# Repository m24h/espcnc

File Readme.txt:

A 3D printer or CNC controller using ESP32 module
Using DMA/FIFO buffered I2S port to output step pulses

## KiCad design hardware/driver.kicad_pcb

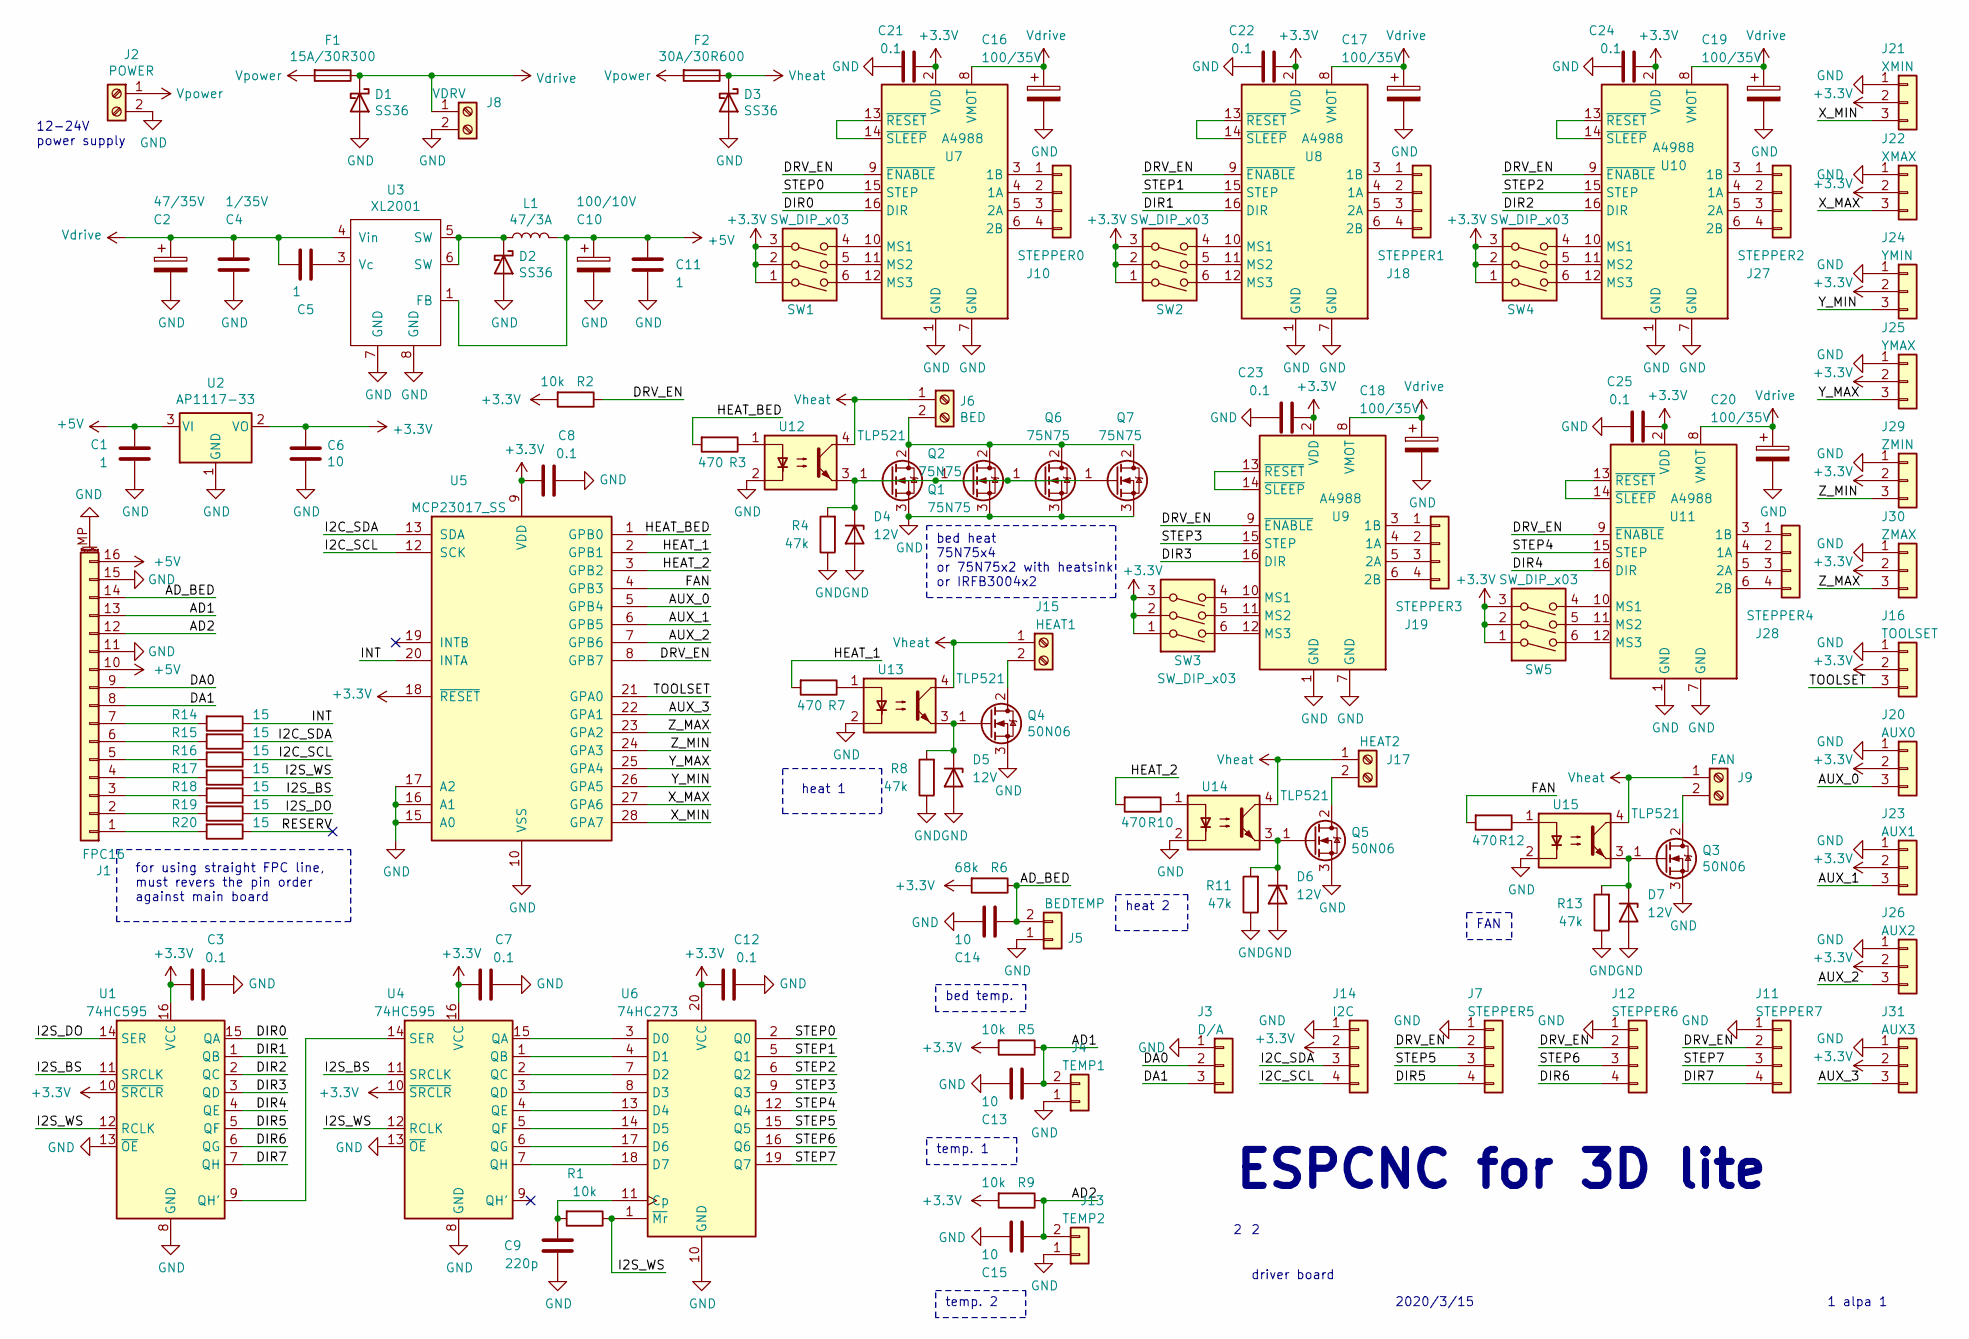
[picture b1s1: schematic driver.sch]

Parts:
C1, C5, C11: 1; C_0805_2012Metric_Pad1.15x1.40mm_HandSolder
C2: 47/35V; CP_Radial_D6.3mm_P2.50mm
C3, C7, C8, C12, C21, C22, C23, C24, C25: 0.1; C_0603_1608Metric_Pad1.05x0.95mm_HandSolder
C4: 1/35V; C_0805_2012Metric_Pad1.15x1.40mm_HandSolder
C6, C13, C14, C15: 10; C_1206_3216Metric_Pad1.42x1.75mm_HandSolder
C9: 220p; C_0603_1608Metric_Pad1.05x0.95mm_HandSolder
C10: 100/10V; CP_Radial_D6.3mm_P2.50mm
C16, C17, C18, C19, C20: 100/35V; CP_Radial_D6.3mm_P2.50mm
D1, D2, D3: SS36; D_SMA_Handsoldering
D4, D5, D6, D7: 12V; D_DO-41_SOD81_P2.54mm_Vertical_KathodeUp
F1: 15A/30R300; Fuse_Bourns_MF-RG300
F2: 30A/30R600; Fuse_Bourns_MF-RG500
J1: FPC16; Molex_200528-0160_1x16-1MP_P1.00mm_Horizontal
J2: POWER; TerminalBlock_bornier-2_P5.08mm
J3: D/A; PinHeader_1x03_P2.54mm_Vertical
J4: TEMP1; PinHeader_1x02_P2.54mm_Vertical
J5: BEDTEMP; PinHeader_1x02_P2.54mm_Vertical
J6: BED; TerminalBlock_bornier-2_P5.08mm
J7: STEPPER5; PinHeader_1x04_P2.54mm_Vertical
J8: VDRV; TerminalBlock_bornier-2_P5.08mm
J9: FAN; TerminalBlock_bornier-2_P5.08mm
J10: STEPPER0; PinHeader_1x04_P2.54mm_Vertical
J11: STEPPER7; PinHeader_1x04_P2.54mm_Vertical
J12: STEPPER6; PinHeader_1x04_P2.54mm_Vertical
J13: TEMP2; PinHeader_1x02_P2.54mm_Vertical
J14: I2C; PinHeader_1x04_P2.54mm_Vertical
J15: HEAT1; TerminalBlock_bornier-2_P5.08mm
J16: TOOLSET; PinHeader_1x03_P2.54mm_Vertical
J17: HEAT2; TerminalBlock_bornier-2_P5.08mm
J18: STEPPER1; PinHeader_1x04_P2.54mm_Vertical
J19: STEPPER3; PinHeader_1x04_P2.54mm_Vertical
J20: AUX0; PinHeader_1x03_P2.54mm_Vertical
J21: XMIN; PinHeader_1x03_P2.54mm_Vertical
J22: XMAX; PinHeader_1x03_P2.54mm_Vertical
J23: AUX1; PinHeader_1x03_P2.54mm_Vertical
J24: YMIN; PinHeader_1x03_P2.54mm_Vertical
J25: YMAX; PinHeader_1x03_P2.54mm_Vertical
J26: AUX2; PinHeader_1x03_P2.54mm_Vertical
J27: STEPPER2; PinHeader_1x04_P2.54mm_Vertical
J28: STEPPER4; PinHeader_1x04_P2.54mm_Vertical
J29: ZMIN; PinHeader_1x03_P2.54mm_Vertical
J30: ZMAX; PinHeader_1x03_P2.54mm_Vertical
J31: AUX3; PinHeader_1x03_P2.54mm_Vertical
L1: 47/3A; L_Toroid_Horizontal_D7.8mm_P13.00mm_Diameter9-5mm_Amidon-T30
Q1, Q2, Q6, Q7: 75N75; TO-220-3_Vertical
Q3, Q4, Q5: 50N06; TO-220-3_Vertical
R1, R2, R5, R9: 10k; R_0603_1608Metric_Pad1.05x0.95mm_HandSolder
R3, R7, R10, R12: 470; R_0603_1608Metric_Pad1.05x0.95mm_HandSolder
R4, R8, R11, R13: 47k; R_0603_1608Metric_Pad1.05x0.95mm_HandSolder
R6: 68k; R_0603_1608Metric_Pad1.05x0.95mm_HandSolder
R14, R15, R16, R17, R18, R19, R20: 15; R_0603_1608Metric_Pad1.05x0.95mm_HandSolder
SW1, SW2, SW3, SW4, SW5: SW_DIP_x03; DIP-6_W7.62mm
U1, U4: 74HC595; SOP-16_4.55x10.3mm_P1.27mm
U2: AP1117-33; SOT-223-3_TabPin2
U3: XL2001; SOP-8_5.28x5.23mm_P1.27mm
U5: MCP23017_SS; SSOP-28_5.3x10.2mm_P0.65mm
U6: 74HC273; SOIC-20W_7.5x12.8mm_P1.27mm
U7, U8, U9, U10, U11: A4988; Pololu_Breakout-16_15.2x20.3mm
U12, U13, U14, U15: TLP521; DIP-4_W7.62mm

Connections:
+3V3: C3.2, C6.1, C7.2, C8.2, C12.2, C21.1, C22.1, C23.1, C24.1, C25.1, J14.2, J16.2, J20.2, J21.2, J22.2, J23.2, J24.2, J25.2, J26.2, J29.2, J30.2, J31.2, R2.2, R5.2, R6.2, R9.2, SW1.1, SW1.2, SW1.3, SW2.1, SW2.2, SW2.3, SW3.1, SW3.2, SW3.3, SW4.1, SW4.2, SW4.3, SW5.1, SW5.2, SW5.3, U1.10 (~SRCLR), U1.16 (VCC), U2.2 (VO), U4.10 (~SRCLR), U4.16 (VCC), U5.9 (VDD), U5.18 (~RESET~), U6.20 (VCC), U7.2 (VDD), U8.2 (VDD), U9.2 (VDD), U10.2 (VDD), U11.2 (VDD)
+5V: C1.1, C10.1, C11.1, J1.10, J1.16, L1.2, U2.3 (VI), U3.1 (FB)
/AD1: C13.1, J1.13, J4.2, R5.1
/AD2: C15.1, J1.12, J13.2, R9.1
/AD_BED: C14.1, J1.14, J5.2, R6.1
/AUX_0: J20.3, U5.5 (GPB4)
/AUX_1: J23.3, U5.6 (GPB5)
/AUX_2: J26.3, U5.7 (GPB6)
/AUX_3: J31.3, U5.22 (GPA1)
/DA0: J1.9, J3.2
/DA1: J1.8, J3.3
/DIR0: U1.15 (QA), U7.16 (DIR)
/DIR1: U1.1 (QB), U8.16 (DIR)
/DIR2: U1.2 (QC), U10.16 (DIR)
/DIR3: U1.3 (QD), U9.16 (DIR)
/DIR4: U1.4 (QE), U11.16 (DIR)
/DIR5: J7.4, U1.5 (QF)
/DIR6: J12.4, U1.6 (QG)
/DIR7: J11.4, U1.7 (QH)
/DRV_EN: J7.2, J11.2, J12.2, R2.1, U5.8 (GPB7), U7.9 (~ENABLE), U8.9 (~ENABLE), U9.9 (~ENABLE), U10.9 (~ENABLE), U11.9 (~ENABLE)
/FAN: R12.2, U5.4 (GPB3)
/HEAT_1: R7.2, U5.2 (GPB1)
/HEAT_2: R10.2, U5.3 (GPB2)
/HEAT_BED: R3.2, U5.1 (GPB0)
/I2C_SCL: J14.4, R16.1, U5.12 (SCK)
/I2C_SDA: J14.3, R15.1, U5.13 (SDA)
/I2S_BS: R18.1, U1.11 (SRCLK), U4.11 (SRCLK)
/I2S_DO: R19.1, U1.14 (SER)
/I2S_WS: R1.1, R17.1, U1.12 (RCLK), U4.12 (RCLK), U6.1 (~Mr)
/INT: R14.1, U5.20 (INTA)
/RESERV: R20.1
/STEP0: U6.2 (Q0), U7.15 (STEP)
/STEP1: U6.5 (Q1), U8.15 (STEP)
/STEP2: U6.6 (Q2), U10.15 (STEP)
/STEP3: U6.9 (Q3), U9.15 (STEP)
/STEP4: U6.12 (Q4), U11.15 (STEP)
/STEP5: J7.3, U6.15 (Q5)
/STEP6: J12.3, U6.16 (Q6)
/STEP7: J11.3, U6.19 (Q7)
/TOOLSET: J16.3, U5.21 (GPA0)
/X_MAX: J22.3, U5.27 (GPA6)
/X_MIN: J21.3, U5.28 (GPA7)
/Y_MAX: J25.3, U5.25 (GPA4)
/Y_MIN: J24.3, U5.26 (GPA5)
/Z_MAX: J30.3, U5.23 (GPA2)
/Z_MIN: J29.3, U5.24 (GPA3)
GND: C1.2, C2.2, C3.1, C4.2, C6.2, C7.1, C8.1, C9.1, C10.2, C11.2, C12.1, C13.2, C14.2, C15.2, C16.2, C17.2, C18.2, C19.2, C20.2, C21.2, C22.2, C23.2, C24.2, C25.2, D1.2 (A), D2.2 (A), D3.2 (A), D4.2 (A), D5.2 (A), D6.2 (A), D7.2 (A), J1.11, J1.15, J1.MP (MountPin), J2.2, J3.1, J4.1, J5.1, J7.1, J8.2, J11.1, J12.1, J13.1, J14.1, J16.1, J20.1, J21.1, J22.1, J23.1, J24.1, J25.1, J26.1, J29.1, J30.1, J31.1, Q1.3 (S), Q2.3 (S), Q3.3 (S), Q4.3 (S), Q5.3 (S), Q6.3 (S), Q7.3 (S), R4.1, R8.1, R11.1, R13.1, U1.8 (GND), U1.13 (~OE), U2.1 (GND), U3.7 (GND), U3.8 (GND), U4.8 (GND), U4.13 (~OE), U5.10 (VSS), U5.15 (A0), U5.16 (A1), U5.17 (A2), U6.10 (GND), U7.1 (GND), U7.7 (GND), U8.1 (GND), U8.7 (GND), U9.1 (GND), U9.7 (GND), U10.1 (GND), U10.7 (GND), U11.1 (GND), U11.7 (GND), U12.2, U13.2, U14.2, U15.2
unnamed: C5.1, U3.3 (Vc)
unnamed: C9.2, R1.2, U6.11 (Cp)
unnamed: D2.1 (K), L1.1, U3.5 (SW), U3.6 (SW)
unnamed: D4.1 (K), Q1.1 (G), Q2.1 (G), Q6.1 (G), Q7.1 (G), R4.2, U12.3
unnamed: D5.1 (K), Q4.1 (G), R8.2, U13.3
unnamed: D6.1 (K), Q5.1 (G), R11.2, U14.3
unnamed: D7.1 (K), Q3.1 (G), R13.2, U15.3
unnamed: J1.1, R20.2
unnamed: J1.2, R19.2
unnamed: J1.3, R18.2
unnamed: J1.4, R17.2
unnamed: J1.5, R16.2
unnamed: J1.6, R15.2
unnamed: J1.7, R14.2
unnamed: J6.2, Q1.2 (D), Q2.2 (D), Q6.2 (D), Q7.2 (D)
unnamed: J9.2, Q3.2 (D)
unnamed: J10.1, U7.3 (1B)
unnamed: J10.2, U7.4 (1A)
unnamed: J10.3, U7.5 (2A)
unnamed: J10.4, U7.6 (2B)
unnamed: J15.2, Q4.2 (D)
unnamed: J17.2, Q5.2 (D)
unnamed: J18.1, U8.3 (1B)
unnamed: J18.2, U8.4 (1A)
unnamed: J18.3, U8.5 (2A)
unnamed: J18.4, U8.6 (2B)
unnamed: J19.1, U9.3 (1B)
unnamed: J19.2, U9.4 (1A)
unnamed: J19.3, U9.5 (2A)
unnamed: J19.4, U9.6 (2B)
unnamed: J27.1, U10.3 (1B)
unnamed: J27.2, U10.4 (1A)
unnamed: J27.3, U10.5 (2A)
unnamed: J27.4, U10.6 (2B)
unnamed: J28.1, U11.3 (1B)
unnamed: J28.2, U11.4 (1A)
unnamed: J28.3, U11.5 (2A)
unnamed: J28.4, U11.6 (2B)
unnamed: R3.1, U12.1
unnamed: R7.1, U13.1
unnamed: R10.1, U14.1
unnamed: R12.1, U15.1
unnamed: SW1.4, U7.10 (MS1)
unnamed: SW1.5, U7.11 (MS2)
unnamed: SW1.6, U7.12 (MS3)
unnamed: SW2.4, U8.10 (MS1)
unnamed: SW2.5, U8.11 (MS2)
unnamed: SW2.6, U8.12 (MS3)
unnamed: SW3.4, U9.10 (MS1)
unnamed: SW3.5, U9.11 (MS2)
unnamed: SW3.6, U9.12 (MS3)
unnamed: SW4.4, U10.10 (MS1)
unnamed: SW4.5, U10.11 (MS2)
unnamed: SW4.6, U10.12 (MS3)
unnamed: SW5.4, U11.10 (MS1)
unnamed: SW5.5, U11.11 (MS2)
unnamed: SW5.6, U11.12 (MS3)
unnamed: U1.9 (QH'), U4.14 (SER)
unnamed: U4.1 (QB), U6.4 (D1)
unnamed: U4.2 (QC), U6.7 (D2)
unnamed: U4.3 (QD), U6.8 (D3)
unnamed: U4.4 (QE), U6.13 (D4)
unnamed: U4.5 (QF), U6.14 (D5)
unnamed: U4.6 (QG), U6.17 (D6)
unnamed: U4.7 (QH), U6.18 (D7)
unnamed: U4.15 (QA), U6.3 (D0)
unnamed: U7.13 (~RESET), U7.14 (~SLEEP)
unnamed: U8.13 (~RESET), U8.14 (~SLEEP)
unnamed: U9.13 (~RESET), U9.14 (~SLEEP)
unnamed: U10.13 (~RESET), U10.14 (~SLEEP)
unnamed: U11.13 (~RESET), U11.14 (~SLEEP)
Vdrive: C2.1, C4.1, C5.2, C16.1, C17.1, C18.1, C19.1, C20.1, D1.1 (K), F1.1, J8.1, U3.4 (Vin), U7.8 (VMOT), U8.8 (VMOT), U9.8 (VMOT), U10.8 (VMOT), U11.8 (VMOT)
Vheat: D3.1 (K), F2.1, J6.1, J9.1, J15.1, J17.1, U12.4, U13.4, U14.4, U15.4
Vpower: F1.2, F2.2, J2.1

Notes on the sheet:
ESPCNC for 3D lite
2020/3/15
driver board
1 alpa 1
bed temp.
12-24V power supply
bed heat 75N75x4 or 75N75x2 with heatsink or IRFB3004x2
heat 2
heat 1
temp. 1
temp. 2
FAN
for using straight FPC line, must revers the pin order against main board

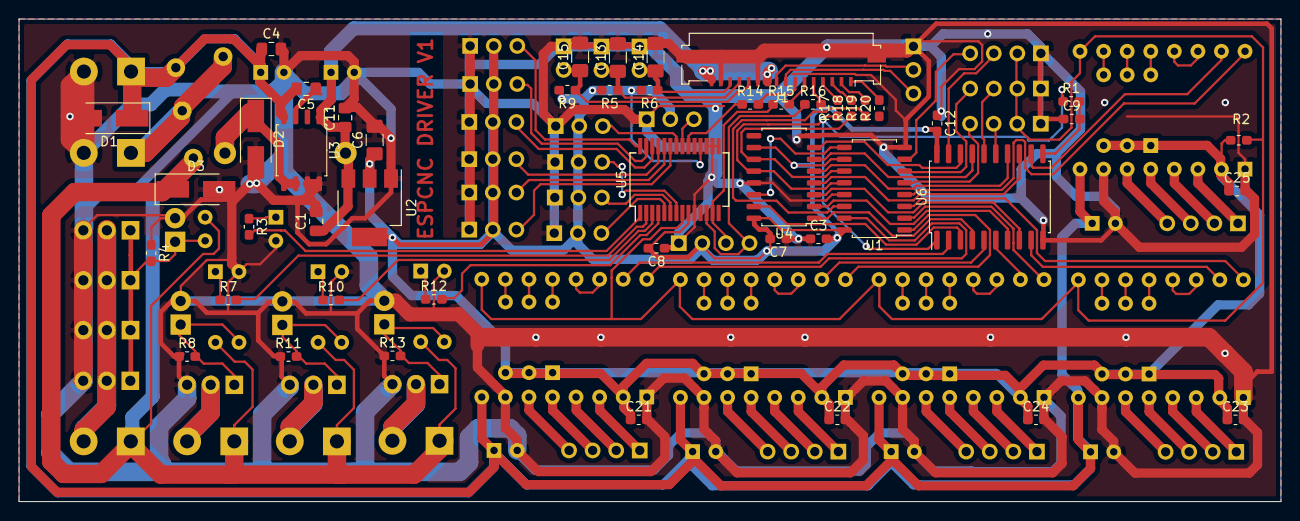
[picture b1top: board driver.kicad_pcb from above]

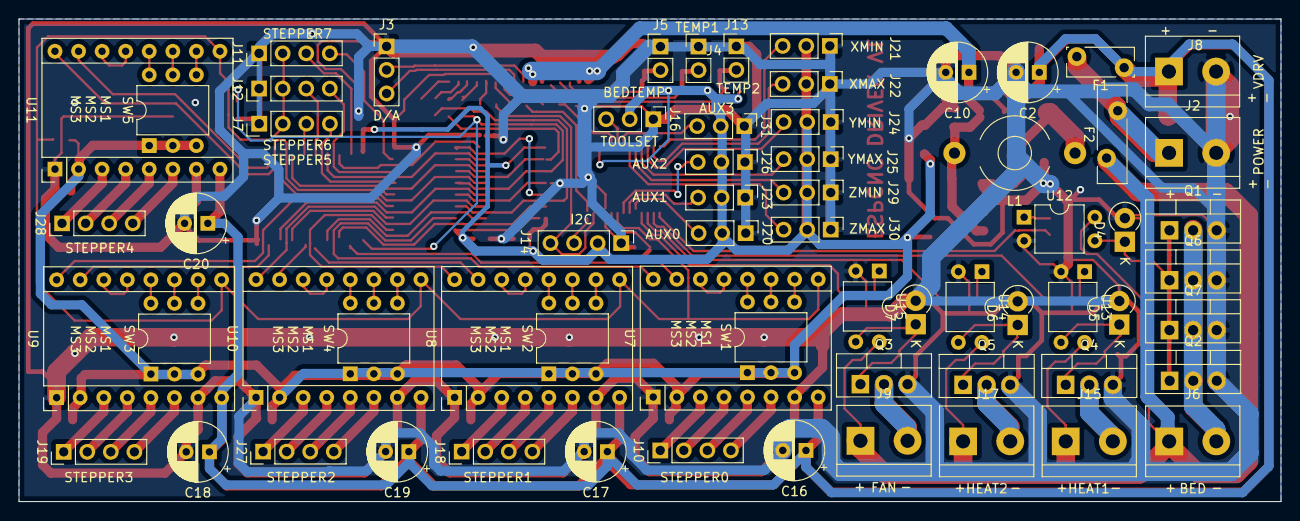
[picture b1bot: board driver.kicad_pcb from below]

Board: 2 copper layers, 136.0 x 52.0 mm, 113 parts (65 on the bottom side), 120 nets.

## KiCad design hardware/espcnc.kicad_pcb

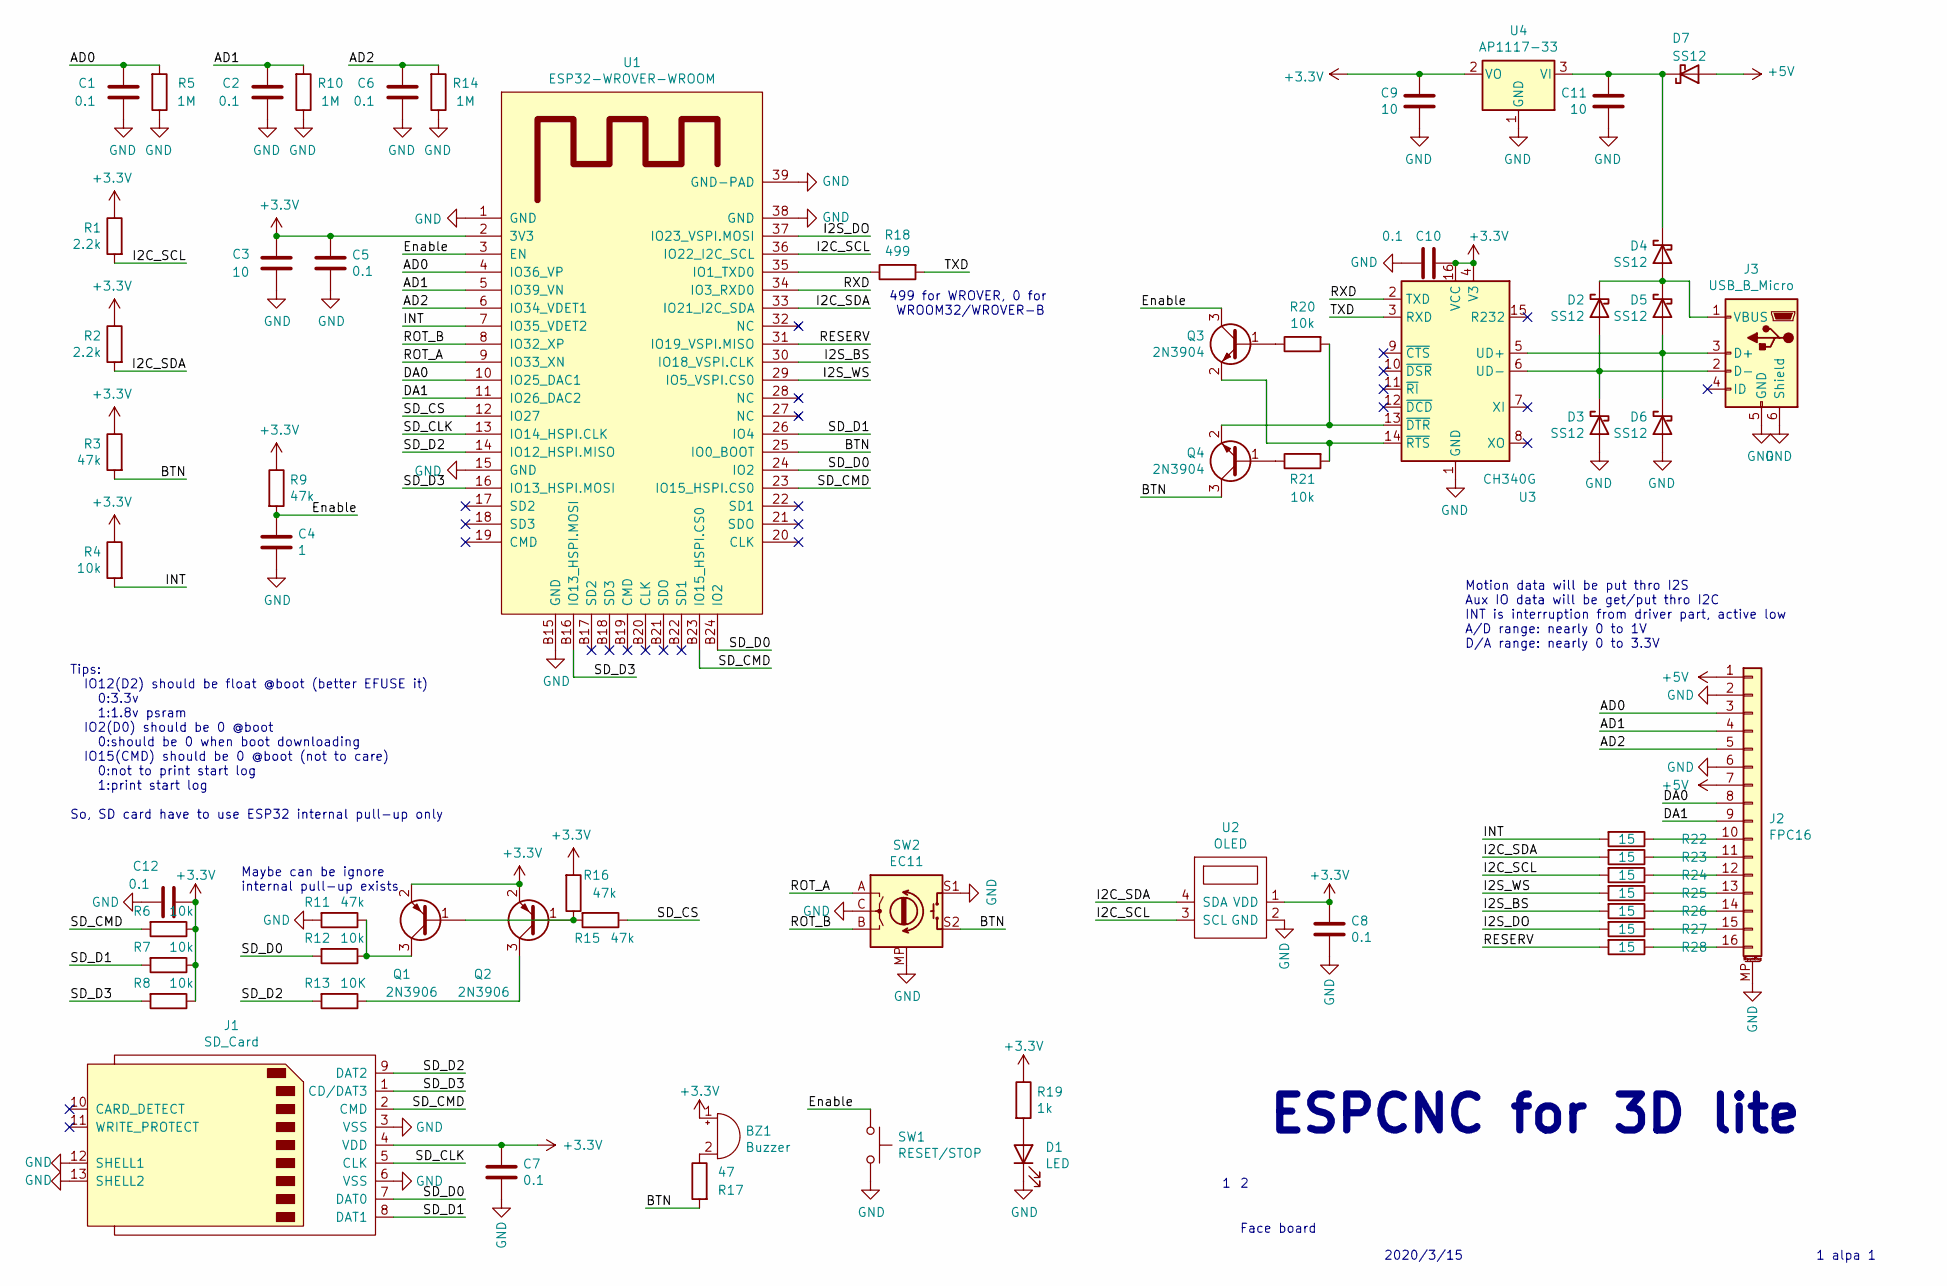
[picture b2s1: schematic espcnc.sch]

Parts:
BZ1: Buzzer; Buzzer_12x9.5RM7.6
C1, C2, C5, C6, C7, C8, C10, C12: 0.1; C_0603_1608Metric_Pad1.05x0.95mm_HandSolder
C3, C9, C11: 10; C_1206_3216Metric_Pad1.42x1.75mm_HandSolder
C4: 1; C_0805_2012Metric_Pad1.15x1.40mm_HandSolder
D1: LED; LED_D1.8mm_W3.3mm_H2.4mm
D2, D3, D4, D5, D6, D7: SS12; D_SMA_Handsoldering
J1: SD_Card; SD_CARD
J2: FPC16; Molex_200528-0160_1x16-1MP_P1.00mm_Horizontal
J3: USB_B_Micro; USB_Micro-B_Molex-105017-0001
Q1, Q2: 2N3906; SOT-23
Q3, Q4: 2N3904; SOT-23
R1, R2: 2.2k; R_0603_1608Metric_Pad1.05x0.95mm_HandSolder
R3, R9, R11, R15, R16: 47k; R_0603_1608Metric_Pad1.05x0.95mm_HandSolder
R4, R6, R7, R8, R12, R20, R21: 10k; R_0603_1608Metric_Pad1.05x0.95mm_HandSolder
R5, R10, R14: 1M; R_0603_1608Metric_Pad1.05x0.95mm_HandSolder
R13: 10K; R_0603_1608Metric_Pad1.05x0.95mm_HandSolder
R17: 47; R_0603_1608Metric_Pad1.05x0.95mm_HandSolder
R18: 499; R_0603_1608Metric_Pad1.05x0.95mm_HandSolder
R19: 1k; R_0603_1608Metric_Pad1.05x0.95mm_HandSolder
R22, R23, R24, R25, R26, R27, R28: 15; R_0603_1608Metric_Pad1.05x0.95mm_HandSolder
SW1: RESET/STOP; SW_PUSH-12mm
SW2: EC11; RotaryEncoder_Alps_EC11E-Switch_Vertical_H20mm_CircularMoun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
U1: ESP32-WROVER-WROOM
U2: OLED; 1.3_inch_i2c_oled_128x64_jinyichen
U3: CH340G; SOP-16_4.4x10.4mm_P1.27mm
U4: AP1117-33; SOT-223-3_TabPin2

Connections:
+3V3: BZ1.1 (-), C3.1, C5.1, C7.1, C8.1, C9.1, C10.2, C12.2, J1.4 (VDD), Q1.2 (E), Q2.2 (E), R1.1, R2.1, R3.1, R4.1, R6.1, R7.1, R8.1, R9.1, R16.2, R19.1, U1.2 (3V3), U2.1 (VDD), U3.4 (V3), U3.16 (VCC), U4.2 (VO)
+5V: D7.2 (A), J2.1, J2.7
/AD0: C1.1, J2.3, R5.2, U1.4 (IO36_VP)
/AD1: C2.1, J2.4, R10.2, U1.5 (IO39_VN)
/AD2: C6.1, J2.5, R14.2, U1.6 (IO34_VDET1)
/BTN: Q4.3 (C), R3.2, R17.2, SW2.S2, U1.25 (IO0_BOOT)
/DA0: J2.8, U1.10 (IO25_DAC1)
/DA1: J2.9, U1.11 (IO26_DAC2)
/Enable: C4.1, Q3.3 (C), R9.2, SW1.1, U1.3 (EN)
/I2C_SCL: R1.2, R24.2, U1.36 (IO22_I2C_SCL), U2.3 (SCL)
/I2C_SDA: R2.2, R23.2, U1.33 (IO21_I2C_SDA), U2.4 (SDA)
/I2S_BS: R26.2, U1.30 (IO18_VSPI.CLK)
/I2S_DO: R27.2, U1.37 (IO23_VSPI.MOSI)
/I2S_WS: R25.2, U1.29 (IO5_VSPI.CS0)
/INT: R4.2, R22.2, U1.7 (IO35_VDET2)
/RESERV: R28.2, U1.31 (IO19_VSPI.MISO)
/ROT_A: SW2.A, U1.9 (IO33_XN)
/ROT_B: SW2.B, U1.8 (IO32_XP)
/RXD: U1.34 (IO3_RXD0), U3.2 (TXD)
/SD_CLK: J1.5 (CLK), U1.13 (IO14_HSPI.CLK)
/SD_CMD: J1.2 (CMD), R6.2, U1.23 (IO15_HSPI.CS0), U1.B23 (IO15_HSPI.CS0)
/SD_CS: R15.1, U1.12 (IO27)
/SD_D0: J1.7 (DAT0), R12.2, U1.24 (IO2), U1.B24 (IO2)
/SD_D1: J1.8 (DAT1), R7.2, U1.26 (IO4)
/SD_D2: J1.9 (DAT2), R13.2, U1.14 (IO12_HSPI.MISO)
/SD_D3: J1.1 (CD/DAT3), R8.2, U1.16 (IO13_HSPI.MOSI), U1.B16 (IO13_HSPI.MOSI)
/TXD: R18.2, U3.3 (RXD)
GND: C1.2, C2.2, C3.2, C4.2, C5.2, C6.2, C7.2, C8.2, C9.2, C10.1, C11.2, C12.1, D1.1 (K), D3.2 (A), D6.2 (A), J1.3 (VSS), J1.6 (VSS), J1.12 (SHELL1), J1.13 (SHELL2), J2.2, J2.6, J2.MP (MountPin), J3.5 (GND), J3.6 (Shield), R5.1, R10.1, R11.2, R14.1, SW1.2, SW2.C, SW2.MP, SW2.S1, U1.1 (GND), U1.15 (GND), U1.38 (GND), U1.39 (GND-PAD), U1.B15 (GND), U2.2 (GND), U3.1 (GND), U4.1 (GND)
unnamed: BZ1.2 (+), R17.1
unnamed: C11.1, D4.1 (K), D7.1 (K), U4.3 (VI)
unnamed: D1.2 (A), R19.2
unnamed: D2.1 (K), D4.2 (A), D5.1 (K), J3.1 (VBUS)
unnamed: D2.2 (A), D3.1 (K), J3.2 (D-), U3.6 (UD-)
unnamed: D5.2 (A), D6.1 (K), J3.3 (D+), U3.5 (UD+)
unnamed: J2.10, R22.1
unnamed: J2.11, R23.1
unnamed: J2.12, R24.1
unnamed: J2.13, R25.1
unnamed: J2.14, R26.1
unnamed: J2.15, R27.1
unnamed: J2.16, R28.1
unnamed: Q1.1 (B), Q2.1 (B), R15.2, R16.1
unnamed: Q1.3 (C), R11.1, R12.1
unnamed: Q2.3 (C), R13.1
unnamed: Q3.1 (B), R20.1
unnamed: Q3.2 (E), R21.2, U3.14 (~RTS)
unnamed: Q4.1 (B), R21.1
unnamed: Q4.2 (E), R20.2, U3.13 (~DTR)
unnamed: R18.1, U1.35 (IO1_TXD0)

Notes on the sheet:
ESPCNC for 3D lite
2020/3/15
Face board
1 alpa 1
499 for WROVER, 0 for WROOM32/WROVER-B
Tips: IO12(D2) should be float @boot (better EFUSE it) 0:3.3v 1:1.8v psram IO2(D0) should be 0 @boot 0:should be 0 when boot downloading IO15(CMD) should be 0 @boot (not to care) 0:not to print start log 1:print start log So, SD card have to use ESP32 internal pull-up only
Maybe can be ignore internal pull-up exists
Motion data will be put thro I2S Aux IO data will be get/put thro I2C INT is interruption from driver part, active low A/D range: nearly 0 to 1V D/A range: nearly 0 to 3.3V

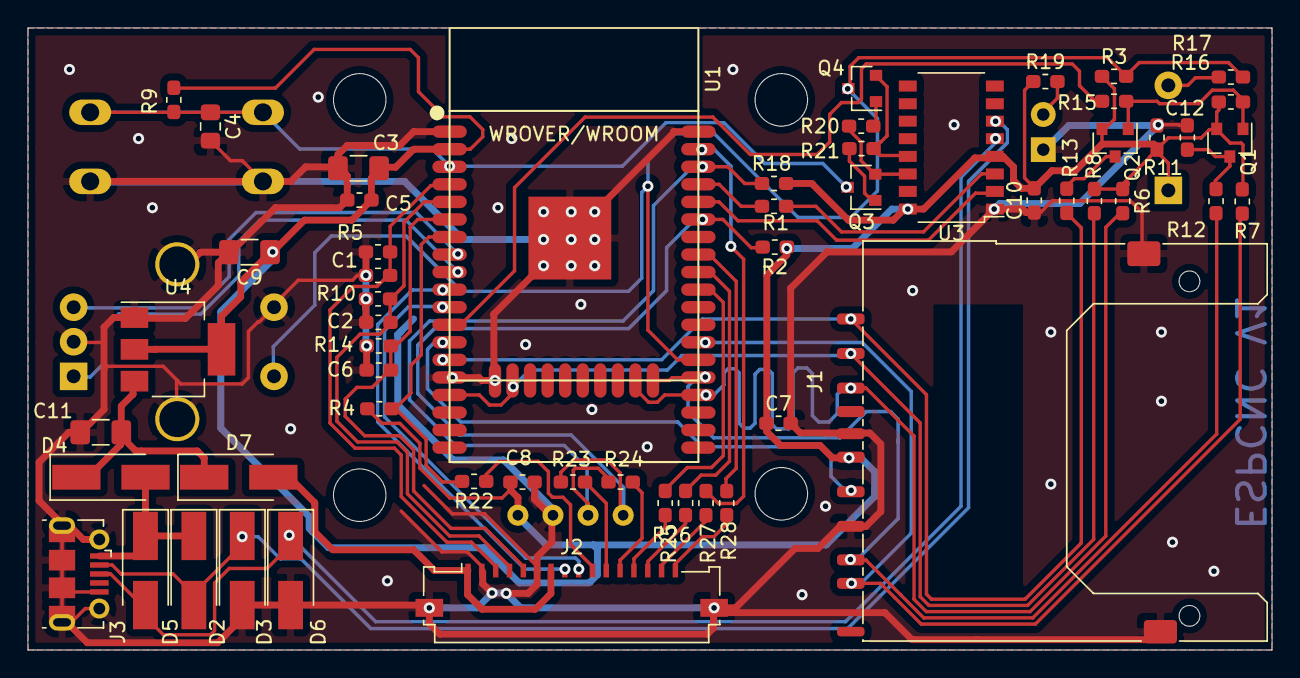
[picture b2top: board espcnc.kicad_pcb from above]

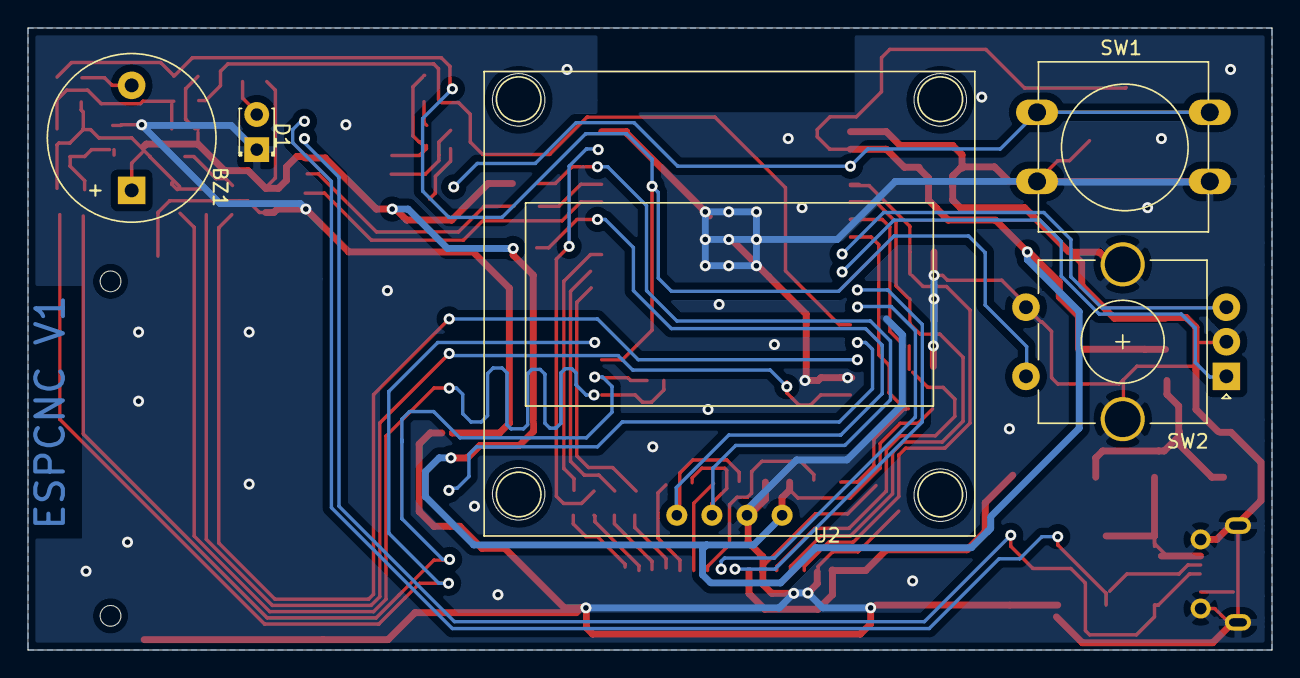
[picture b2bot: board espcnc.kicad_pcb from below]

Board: 2 copper layers, 90.0 x 45.0 mm, 61 parts (5 on the bottom side), 49 nets.

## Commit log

2020-03-20 Trying start
    hardware first, now the sch/pcb is OK
2020-03-20 Added logo to espcnc PCB
2020-03-20 Add comment words on driver pcb silk layer
2020-03-21 removed some unused via holes left on pcb, gerber outputs changed to relative coordinates
